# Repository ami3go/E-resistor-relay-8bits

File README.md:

# E-Resistor Relay 8bits

8-bit relay-based resistor switch board, part of the [E-Resistor](https://github.com/ami3go/E-resistor) project family.

The board is built around the common **YHQ001 eight-channel Ethernet relay board** (WCH CH9120 Ethernet-to-UART controller), switching 8 relay channels to select resistance values.

## Control software

Control software is not duplicated here — it's included as the [control/](control) submodule, pointing at [ch9120-ethernet-relay-toolkit](https://github.com/ami3go/ch9120-ethernet-relay-toolkit), which provides:

- CH9120 discovery over UDP ports 50000/60000.
- Read, back up, modify, write, and verify the CH9120 configuration.
- Tkinter configuration and relay-control GUIs.
- CLI tools for discovery, configuration, TCP-server setup, and relay sequence testing.

### Getting the code

```bash
git clone --recurse-submodules https://github.com/ami3go/E-resistor-relay-8bits.git
```

If already cloned without `--recurse-submodules`:

```bash
git submodule update --init --recursive
```

See [control/README.md](control/README.md) for full relay-control usage instructions.

## Resistance driver

[eresistor_relay8bits/](eresistor_relay8bits) is the Python driver for the board's resistance behavior, implementing [E_Resistor_8Relay_Driver_Spec.md](E_Resistor_8Relay_Driver_Spec.md). It is independent of the relay transport: the resistance model, code<->coil-mask inversion, and channel/bank logic don't know or care how a coil mask actually reaches a board.

One board's 8 relays realize **one channel** (one programmable resistor). A bank can hold up to **128 channels** — i.e. up to 128 boards, each on its own IP.

```bash
pip install -e .          # core driver
pip install -e ./control  # only needed for Ch9120RelayTransport
```

```python
from eresistor_relay8bits import EResistorBank
from eresistor_relay8bits.ch9120_transport import Ch9120RelayTransport

bank = EResistorBank.load_calibration("calibration.json")

bank.add_channel(0, ip="192.168.0.211", transport=Ch9120RelayTransport("192.168.0.211"))
bank.add_channel(1, ip="192.168.0.212", transport=Ch9120RelayTransport("192.168.0.212"))

result = bank[0].set_resistance(15_000)
print(result.code, result.actual_ohm, result.error_percent)

bank.safe_state_all()
```

### Relay transition safety

The real CH9120 transport defaults to a **break-before-make style** update:

1. send **all coils OFF**,
2. optionally wait an interlock delay,
3. energize only the bypass relays required by the target mask.

For this resistor topology, all coils OFF means **all resistor cells inserted**, which is the maximum-resistance state. A transition therefore approaches the requested resistance from above instead of briefly creating an unintended lower resistance.

```python
transport = Ch9120RelayTransport(
    "192.168.0.211",
    break_before_make=True,
    interlock_delay_s=0.02,  # optional; set from measured relay timing
)
```

The default delay is `0.0` seconds because the correct physical relay release/operate timing must be established on the actual board. Use a measured delay for hardware qualification. Setting `break_before_make=False` restores direct per-relay updates and is not recommended for normal resistor switching.

### Examples

[examples/](examples) has runnable, self-contained scripts, from simulated (no hardware needed) to real hardware:

| Script | What it shows | Needs real hardware? |
|---|---|---|
| [01_single_channel.py](examples/01_single_channel.py) | Set one channel to a few target resistances, read back state, safe state | No |
| [02_multi_channel_bank.py](examples/02_multi_channel_bank.py) | Drive several channels through one `EResistorBank` | No |
| [03_calibration_workflow.py](examples/03_calibration_workflow.py) | Apply measured calibration, save it, reload it on another PC | No |
| [04_real_hardware_ch9120.py](examples/04_real_hardware_ch9120.py) | Set a real board's resistance over the network, then return it to safe state | **Yes** |

Run the simulated examples:

```bash
pip install -e .
python examples/01_single_channel.py
python examples/02_multi_channel_bank.py
python examples/03_calibration_workflow.py
```

For real hardware:

```bash
pip install -e ./control
python examples/04_real_hardware_ch9120.py 192.168.0.211 15000
```

This will actually energize relays on that board — disconnect anything sensitive first.

### Calibration

Nominal resistances are computed from 1% resistor values; real boards should be calibrated by measuring the base network and each of the 8 cells. Calibration is keyed by **(IP address, channel id)**, not just channel id.

```python
from eresistor_relay8bits import CalibrationRecord

bank[0].apply_calibration(CalibrationRecord(
    base_ohm=301.4,
    cell_ohm=(2078.0, 4249.9, 8455.1, 16902.7, 33980.1, 67910.3, 135901.5, 270720.8),
    note="measured 2026-09-30",
))
bank.save_calibration("calibration.json")
```

`calibration.json` is a plain JSON file (see [calibration.example.json](calibration.example.json)). The driver resolves each channel's calibration by its `(ip, channel_id)` identity.

### Existing calibration GUI integration

This relay driver can be used directly by the existing
`ami3go/E-resistor-matrix-calibration-tool` PySide6 calibration GUI. The GUI
branch/profile for this board uses the custom switching factory:

```text
eresistor_relay8bits.calibration_adapter:create_switching_adapter
```

The relay topology is **series binary with an always-present base resistor**.
Calibration therefore differs from the original parallel MOSFET matrix:

1. set logical code `0` and measure the base resistance;
2. set each single-bit code and measure `base + cell`;
3. derive each calibrated cell weight as `measured_total - measured_base`;
4. verify combinations with `R = base + sum(selected cells)`;
5. for the normal 300 Ω…400 kΩ profile, verify all **190 application codes
   0…189**.

The calibration GUI writes `relay_driver_calibration.json` in the native
`CalibrationStore` format used by this package. It can be loaded without any
conversion:

```python
from eresistor_relay8bits import EResistorBank

bank = EResistorBank.load_calibration(
    "calibration_output/<serial>/runs/<timestamp>/relay_driver_calibration.json"
)
```

Typical setup:

```bash
# Relay repository
git clone --recurse-submodules https://github.com/ami3go/E-resistor-relay-8bits.git
cd E-resistor-relay-8bits
python -m pip install -e .
python -m pip install -e ./control

# In the calibration-tool repository:
cd dev/resistor_matrix_calibrator_gui
python -m pip install -e .
resistor-matrix-calibrator
```

Load the profile `profiles/e_resistor_relay_8bits.json`, then set the real
relay-board IP address(es) and the HP/Keysight 34401A VISA resource before
running real hardware calibration.

The current GUI exposes eight logical calibration channels, so one GUI run can
calibrate up to eight relay boards. The Python relay bank itself remains
capable of more channels.

The same workflow is available directly from a Linux terminal. Once the
calibration-tool package is installed in the same Python environment, run from
this relay repository:

```bash
python3 scripts/calibrate_linux.py --list-visa

python3 scripts/calibrate_linux.py \
  --check \
  --board 192.168.0.211 \
  --visa 'USB0::0x03EB::0x2065::HEWLETT-PACKARD_34401A_0_11-5-2::INSTR'

python3 scripts/calibrate_linux.py \
  --board 192.168.0.211 \
  --visa 'USB0::0x03EB::0x2065::HEWLETT-PACKARD_34401A_0_11-5-2::INSTR' \
  --serial RELAY-001 \
  --operator "$USER"
```

The installed calibration package also exposes the executable
`e-resistor-calibrate`. Both entry points use the same headless
`CalibrationWorker` as the GUI.

### HIL qualification

A bench-ready HIL package is included under [hil/](hil) with a complete
runbook in [HIL_TEST_PLAN.md](HIL_TEST_PLAN.md).

Prepare the Linux environment and local bench configuration:

```bash
git submodule update --init --recursive
bash hil/setup_linux.sh
source .venv/bin/activate

cp hil/bench.env.example hil/bench.env
nano hil/bench.env
```

Then run the electrical preflight:

```bash
bash hil/preflight.sh
```

The preflight checks:

- physical all-coils-OFF safe state,
- base-only code `0x00`,
- B0...B7 one at a time,
- derived individual cell values,
- application maximum code `0xBD`,
- final return to physical safe state,
- HIL JSON/CSV evidence.

After it passes, run the gated full HIL calibration:

```bash
bash hil/run_full.sh
```

The full script re-runs preflight first and only then starts the complete
base + 8-cell calibration and all **190 application-code verification points**.

Use [hil/HIL_RESULT_TEMPLATE.md](hil/HIL_RESULT_TEMPLATE.md) for the final
board qualification record. The first HIL should be performed with the DUT
disconnected and the 34401A connected directly across the E-Resistor output.

### Tests

```bash
python -m unittest discover -s tests -t . -v
```

GitHub Actions runs the same test suite on Python 3.10, 3.11, 3.12 and 3.13.

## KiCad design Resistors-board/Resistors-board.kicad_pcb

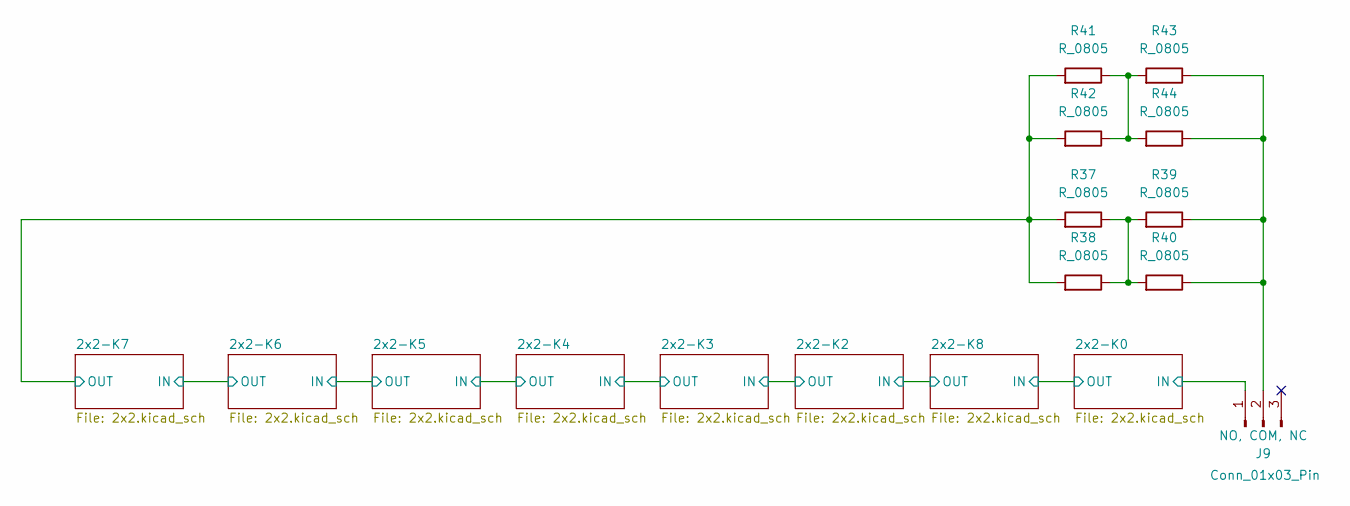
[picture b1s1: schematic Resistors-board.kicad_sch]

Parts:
J9: Conn_01x03_Pin; TerminalBlock_RND_205-00002_1x03_P5.00mm_Horizontal
R37, R38, R39, R40, R41, R42, R43, R44: R_0805; R_0805_2012Metric

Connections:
/2x2-K0/IN: J9.1; also elsewhere on the board
/2x2-K7/OUT: R37.1, R38.1, R41.1, R42.1; also elsewhere on the board
unnamed: J9.2, R39.2, R40.2, R43.2, R44.2
unnamed: R37.2, R38.2, R39.1, R40.1
unnamed: R41.2, R42.2, R43.1, R44.1

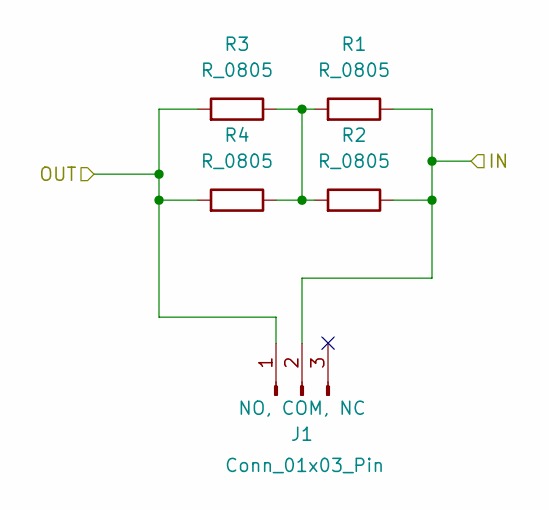
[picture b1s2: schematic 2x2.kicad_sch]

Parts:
J1: Conn_01x03_Pin; TerminalBlock_RND_205-00002_1x03_P5.00mm_Horizontal
R1, R2, R3, R4: R_0805; R_0805_2012Metric

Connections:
/2x2-K0/IN: J1.2, R1.2, R2.2; also elsewhere on the board
/2x2-K0/OUT: J1.1, R3.1, R4.1; also elsewhere on the board
unnamed: R1.1, R2.1, R3.2, R4.2

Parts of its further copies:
J3, J4, J5, J6, J7, J8, J10: Conn_01x03_Pin; TerminalBlock_RND_205-00002_1x03_P5.00mm_Horizontal
R9, R10, R11, R12, R13, R14, R15, R16, R17, R18, R19, R20, R21, R22, R23, R24, R25, R26, R27, R28, R29, R30, R31, R32, R33, R34, R35, R36: R_0805; R_0805_2012Metric

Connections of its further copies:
/2x2-K0/OUT: J10.2, R35.2, R36.2; also elsewhere on the board
/2x2-K2/IN: J3.2, J10.1, R11.2, R12.2, R33.1, R34.1
/2x2-K2/OUT: J3.1, J4.2, R9.1, R10.1, R15.2, R16.2
/2x2-K3/OUT: J4.1, J5.2, R13.1, R14.1, R19.2, R20.2
/2x2-K4/OUT: J5.1, J6.2, R17.1, R18.1, R23.2, R24.2
/2x2-K5/OUT: J6.1, J7.2, R21.1, R22.1, R27.2, R28.2
/2x2-K6/OUT: J7.1, J8.2, R25.1, R26.1, R31.2, R32.2
/2x2-K7/OUT: J8.1, R29.1, R30.1; also elsewhere on the board
unnamed: R9.2, R10.2, R11.1, R12.1
unnamed: R13.2, R14.2, R15.1, R16.1
unnamed: R17.2, R18.2, R19.1, R20.1
unnamed: R21.2, R22.2, R23.1, R24.1
unnamed: R25.2, R26.2, R27.1, R28.1
unnamed: R29.2, R30.2, R31.1, R32.1
unnamed: R33.2, R34.2, R35.1, R36.1

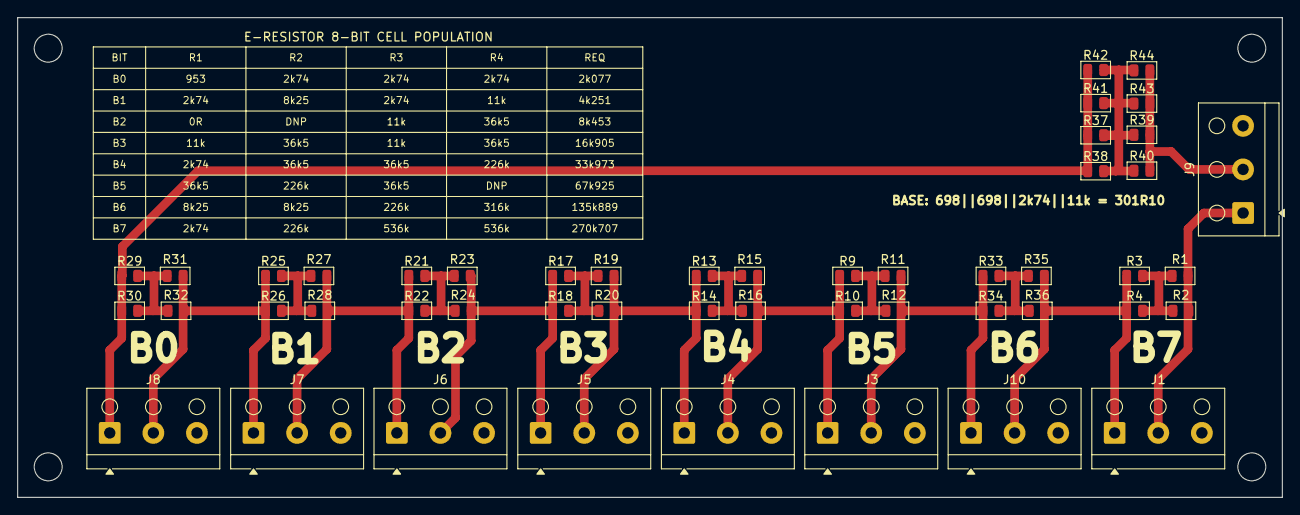
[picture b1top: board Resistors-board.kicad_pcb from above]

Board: 2 copper layers, 145.0 x 55.0 mm, 49 parts (0 on the bottom side), 20 nets.

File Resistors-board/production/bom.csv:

Designator,Footprint,Quantity,Value,LCSC Part #
"J1, J10, J3, J4, J5, J6, J7, J8, J9",TerminalBlock_RND_205-00002_1x03_P5.00mm_Horizontal,9,Conn_01x03_Pin,
"R1, R10, R11, R12, R13, R14, R15, R16, R17, R18, R19, R2, R20, R21, R22, R23, R24, R25, R26, R27, R28, R29, R3, R30, R31, R32, R33, R34, R35, R36, R37, R38, R39, R4, R40, R41, R42, R43, R44, R9",0805,40,R_0805,
